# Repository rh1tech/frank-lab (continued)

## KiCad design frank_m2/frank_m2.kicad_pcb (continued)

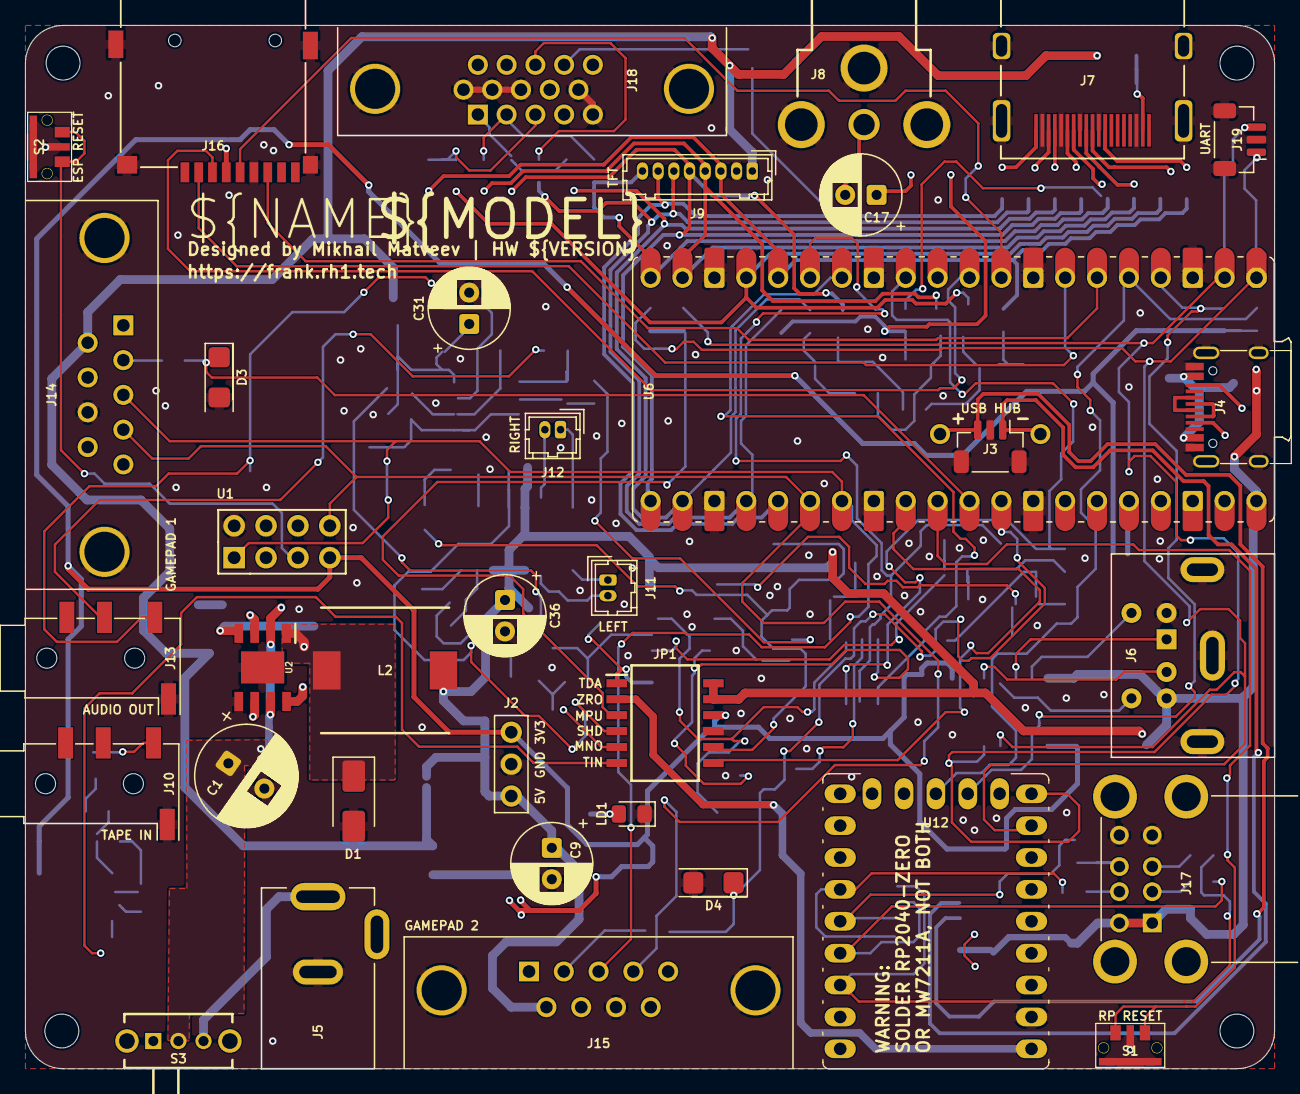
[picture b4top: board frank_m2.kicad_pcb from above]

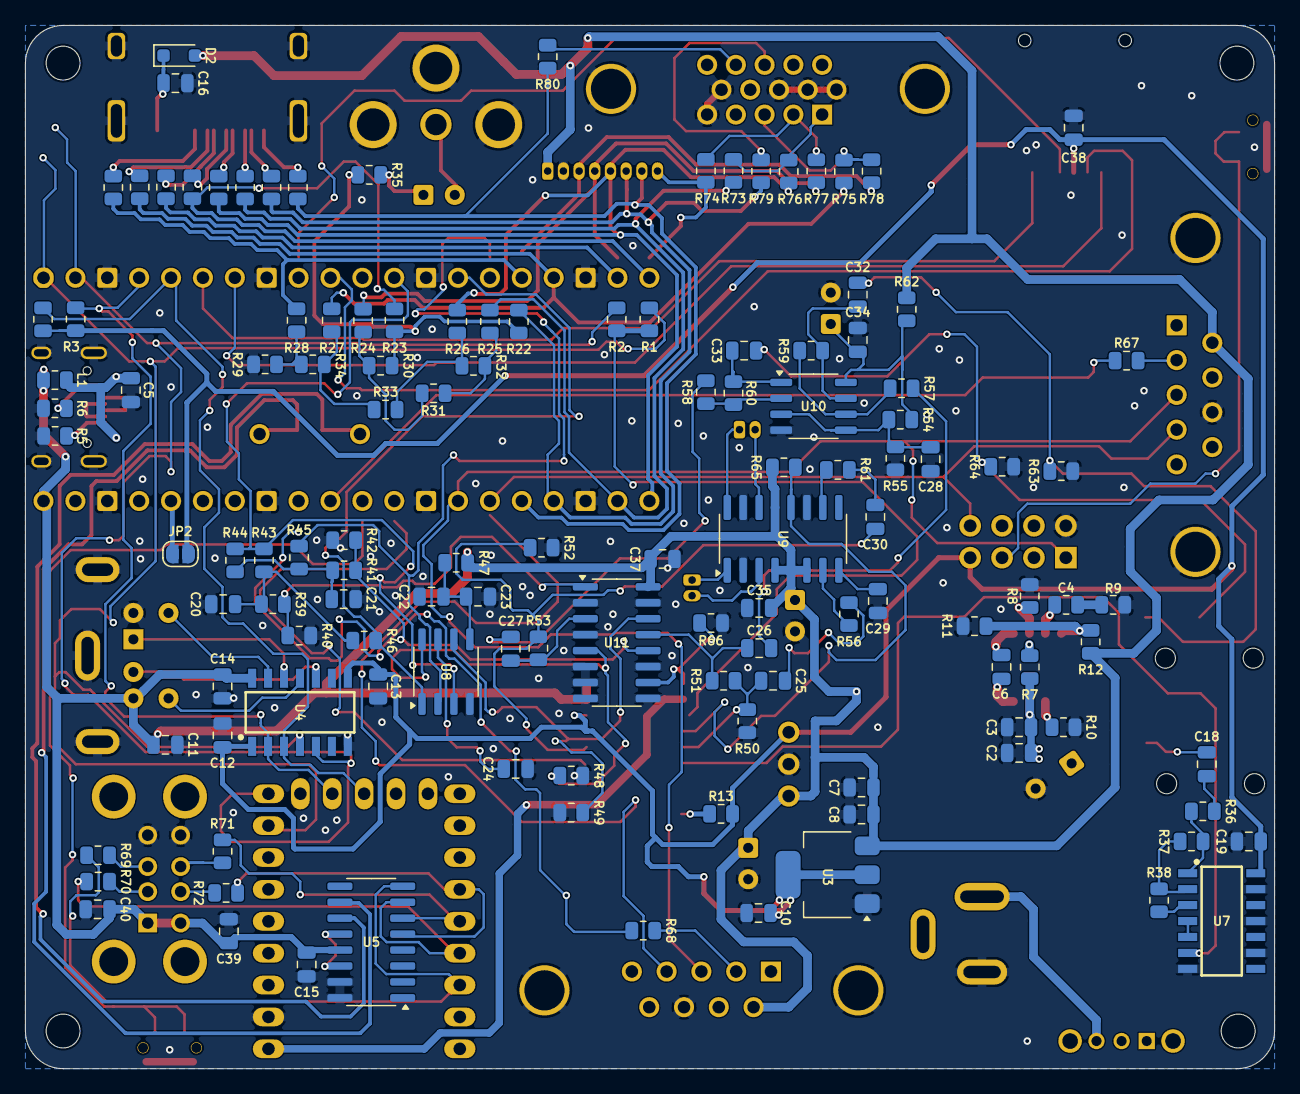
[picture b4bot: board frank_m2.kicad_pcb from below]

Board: 2 copper layers, 99.5 x 83.1 mm, 166 parts (126 on the bottom side), 126 nets.

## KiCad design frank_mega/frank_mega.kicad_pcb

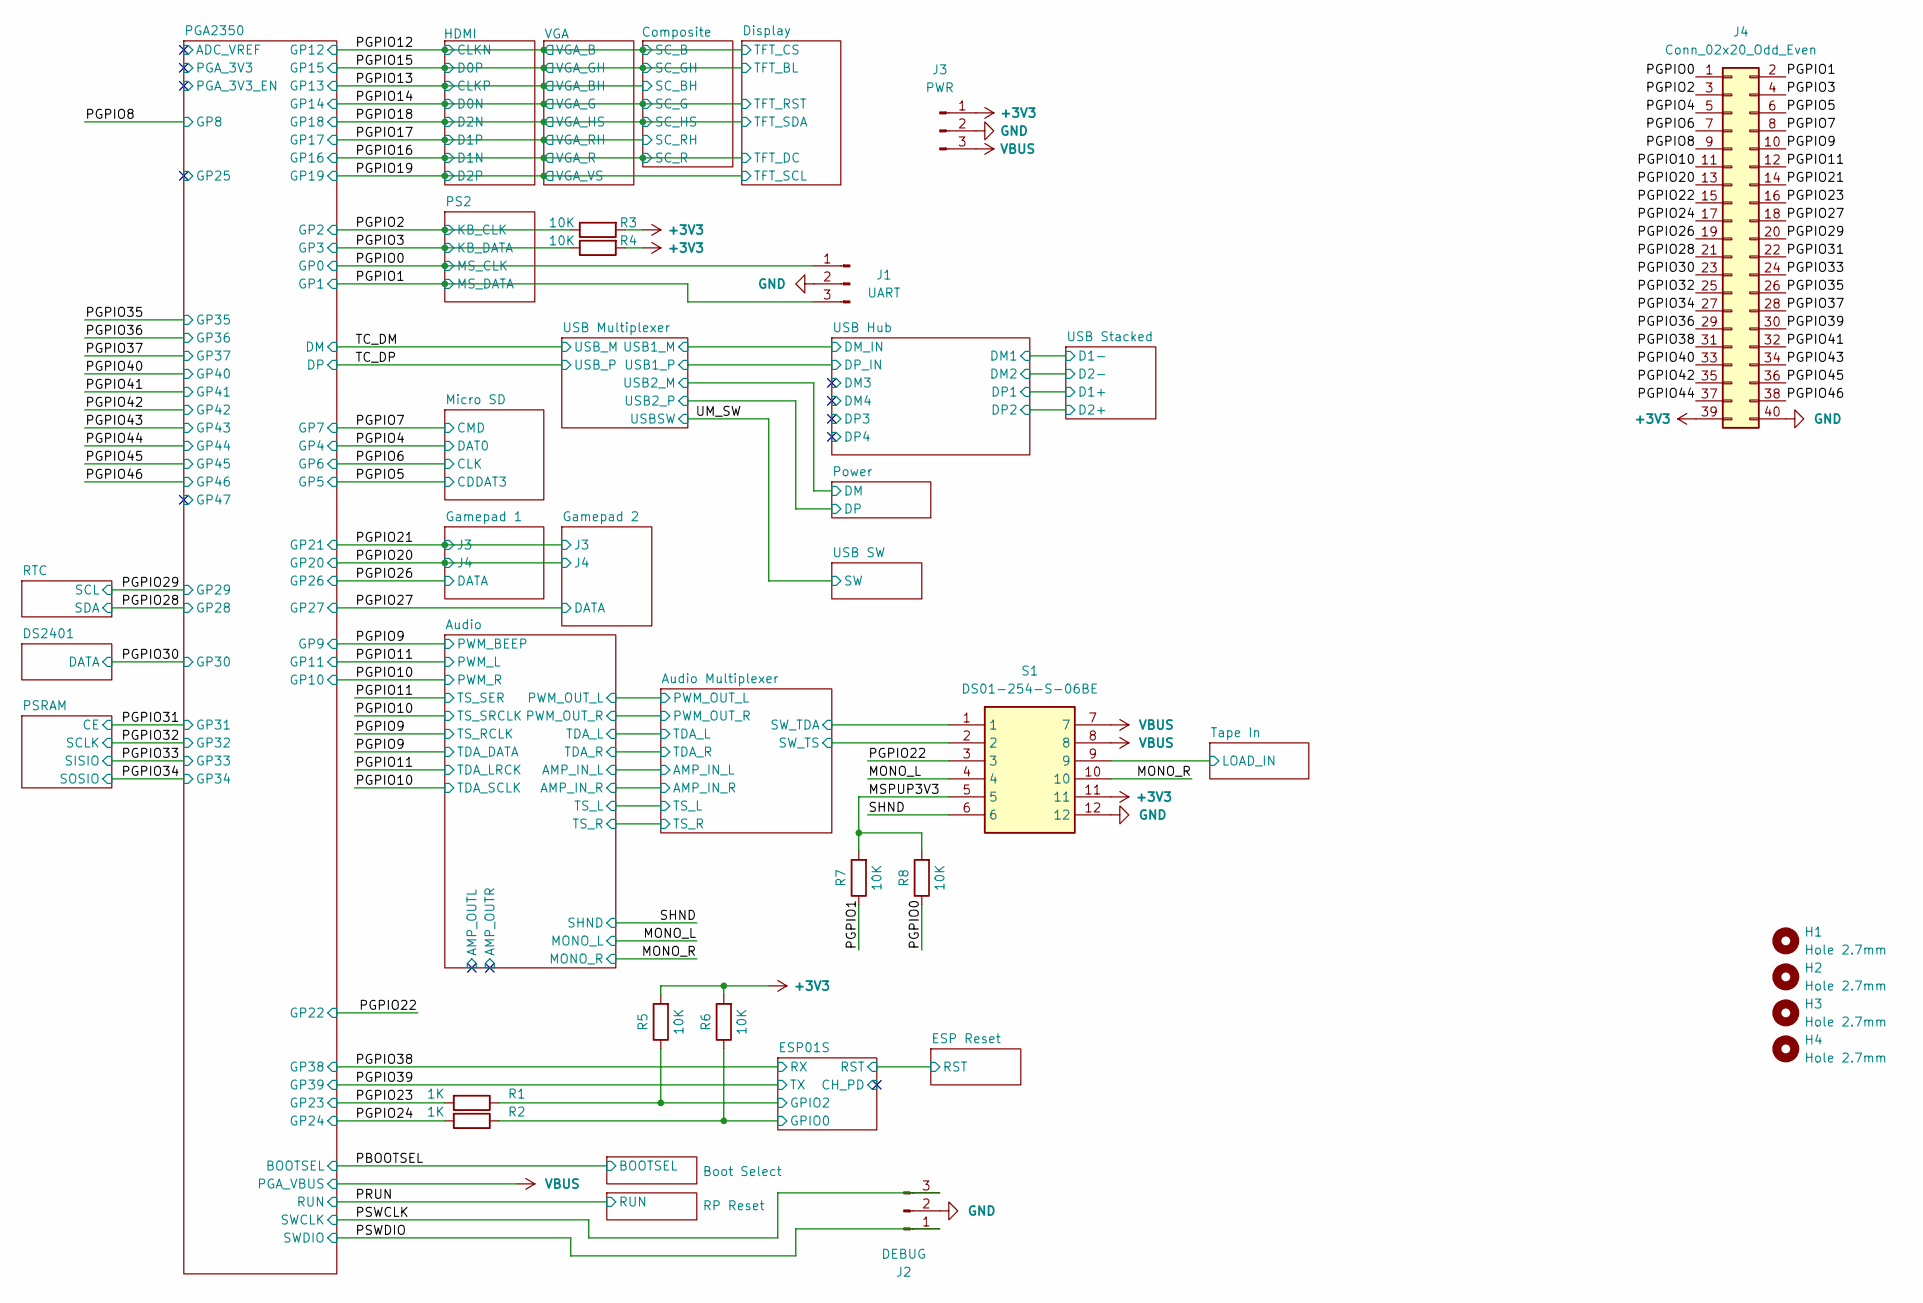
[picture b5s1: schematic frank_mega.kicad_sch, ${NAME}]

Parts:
H1, H2, H3, H4: Hole 2.7mm; MountingHole_2.7mm
J1: UART; JST_SH_1x03_P1.00mm_Vertical
J2: DEBUG; JST_SH_1x03_P1.00mm_Vertical
J3: PWR; PinHeader_1x03_P2.54mm
J4: Conn_02x20_Odd_Even; PinHeader_2x20_P2.54mm_Vertical
R1, R2: 1K; R_0805_2012Metric
R3, R4, R5, R6, R7, R8: 10K; R_0805_2012Metric
S1: DS01-254-S-06BE; Manufacturer_Part_Number DS01-254-S-06BE

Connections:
+3V3: J3.1, J4.39, R3.2, R4.2, R5.2, R6.2, S1.11; also elsewhere on the board
/Audio Multiplexer/SW_TDA: S1.1; also elsewhere on the board
/Audio Multiplexer/SW_TS: S1.2; also elsewhere on the board
/ESP01S/GPIO0: R2.1, R6.1; also elsewhere on the board
/ESP01S/GPIO2: R1.1, R5.1; also elsewhere on the board
/MONO_L: S1.4; also elsewhere on the board
/MONO_R: S1.10; also elsewhere on the board
/MSPUP3V3: R7.2, R8.2, S1.5
/PGPIO0: J1.1, J4.1, R8.1; also elsewhere on the board
/PGPIO1: J1.3, J4.2, R7.1; also elsewhere on the board
/PGPIO2: J4.3, R3.1; also elsewhere on the board
/PGPIO3: J4.4, R4.1; also elsewhere on the board
/PGPIO4: J4.5; also elsewhere on the board
/PGPIO5: J4.6; also elsewhere on the board
/PGPIO6: J4.7; also elsewhere on the board
/PGPIO7: J4.8; also elsewhere on the board
/PGPIO8: J4.9; also elsewhere on the board
/PGPIO9: J4.10; also elsewhere on the board
/PGPIO10: J4.11; also elsewhere on the board
/PGPIO11: J4.12; also elsewhere on the board
/PGPIO20: J4.13; also elsewhere on the board
/PGPIO21: J4.14; also elsewhere on the board
/PGPIO22: J4.15, S1.3; also elsewhere on the board
/PGPIO23: J4.16, R1.2; also elsewhere on the board
/PGPIO24: J4.17, R2.2; also elsewhere on the board
/PGPIO26: J4.19; also elsewhere on the board
/PGPIO27: J4.18; also elsewhere on the board
/PGPIO28: J4.21; also elsewhere on the board
/PGPIO29: J4.20; also elsewhere on the board
/PGPIO30: J4.23; also elsewhere on the board
/PGPIO31: J4.22; also elsewhere on the board
/PGPIO32: J4.25; also elsewhere on the board
/PGPIO33: J4.24; also elsewhere on the board
/PGPIO34: J4.27; also elsewhere on the board
/PGPIO35: J4.26; also elsewhere on the board
/PGPIO36: J4.29; also elsewhere on the board
/PGPIO37: J4.28; also elsewhere on the board
/PGPIO38: J4.31; also elsewhere on the board
/PGPIO39: J4.30; also elsewhere on the board
/PGPIO40: J4.33; also elsewhere on the board
/PGPIO41: J4.32; also elsewhere on the board
/PGPIO42: J4.35; also elsewhere on the board
/PGPIO43: J4.34; also elsewhere on the board
/PGPIO44: J4.37; also elsewhere on the board
/PGPIO45: J4.36; also elsewhere on the board
/PGPIO46: J4.38; also elsewhere on the board
/PSWCLK: J2.3; also elsewhere on the board
/PSWDIO: J2.1; also elsewhere on the board
/SHND: S1.6; also elsewhere on the board
/Tape In/LOAD_IN: S1.9; also elsewhere on the board
GND: J1.2, J2.2, J3.2, J4.40, S1.12; also elsewhere on the board
VBUS: J3.3, S1.7, S1.8; also elsewhere on the board

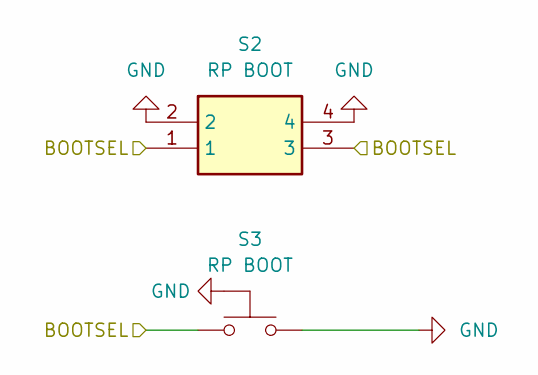
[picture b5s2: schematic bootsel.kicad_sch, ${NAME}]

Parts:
S2: RP BOOT; Button_SMD_3x4x2mm; Mouser Part Number 611-KMR221G-LFS
S3: RP BOOT; Button_SMD_TS1234VW

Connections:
/PBOOTSEL: S2.1, S2.3, S3.1; also elsewhere on the board
GND: S2.2, S2.4, S3.2, S3.3 (GND); also elsewhere on the board

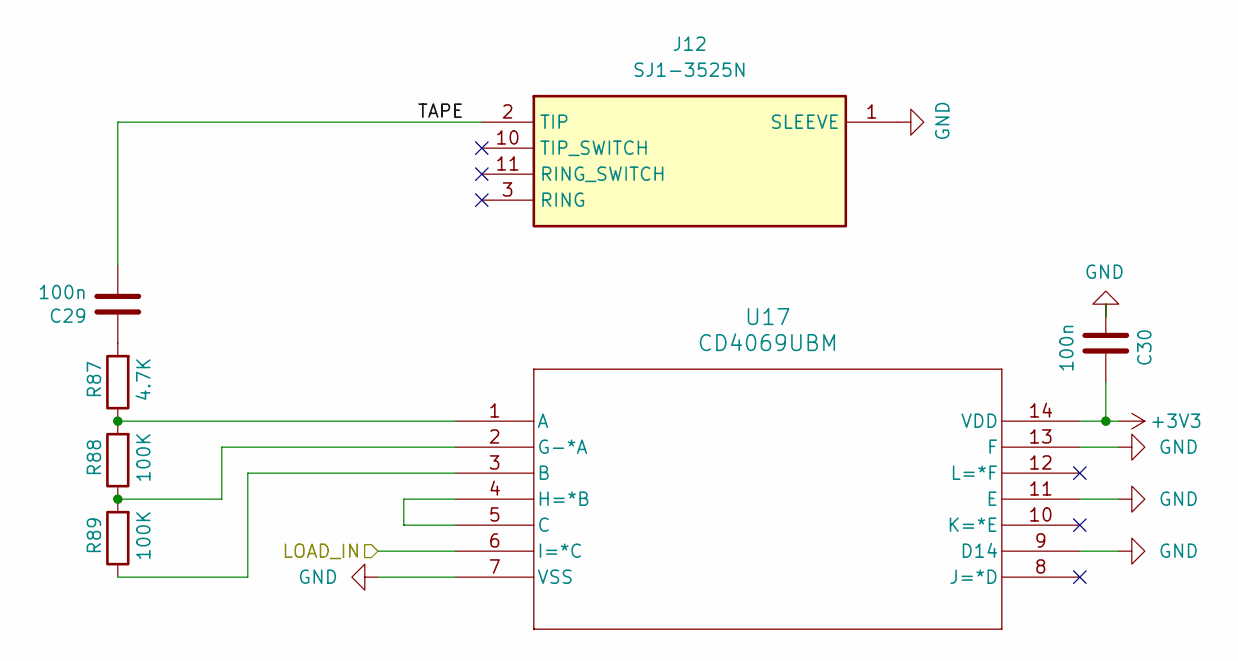
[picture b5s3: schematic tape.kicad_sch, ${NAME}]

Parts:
C29, C30: 100n; C_0805_2012Metric
J12: SJ1-3525N; AudioJack_3.5mm_SJ1-3525N; Mouser Part Number 490-SJ1-3525N
R87: 4.7K; R_0805_2012Metric
R88, R89: 100K; R_0805_2012Metric
U17: CD4069UBM; SOIC-14_P1.27mm

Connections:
+3V3: C30.1, U17.14 (VDD); also elsewhere on the board
/Tape In/LOAD_IN: U17.6 (I=*C); also elsewhere on the board
/Tape In/TAPE: C29.2, J12.2 (TIP)
GND: C30.2, J12.1 (SLEEVE), U17.7 (VSS), U17.9 (D14), U17.11 (E), U17.13 (F); also elsewhere on the board
unnamed: C29.1, R87.2
unnamed: R87.1, R88.2, U17.1 (A)
unnamed: R89.1, U17.3 (B)
unnamed: U17.4 (H=*B), U17.5 (C)
unnamed: R88.1, R89.2, U17.2 (G-*A)

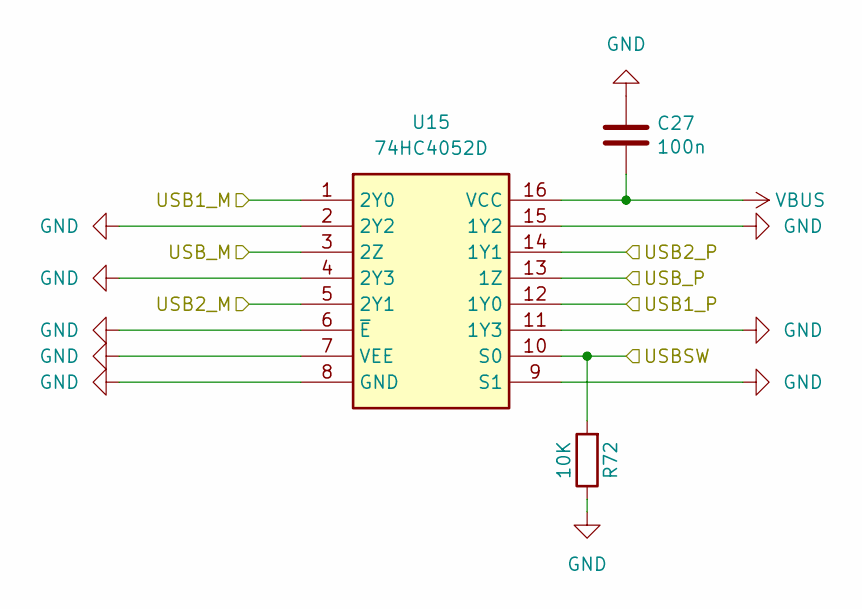
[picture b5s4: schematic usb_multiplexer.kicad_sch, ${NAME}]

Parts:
C27: 100n; C_0805_2012Metric
R72: 10K; R_0805_2012Metric
U15: 74HC4052D; SOP-16_P1.27mm; Mouser Part Number 771-74HC4052D-T

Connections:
/Power/DM: U15.5 (2Y1); also elsewhere on the board
/Power/DP: U15.14 (1Y1); also elsewhere on the board
/TC_DM: U15.3 (2Z); also elsewhere on the board
/TC_DP: U15.13 (1Z); also elsewhere on the board
/UM_SW: R72.2, U15.10 (S0); also elsewhere on the board
/USB Hub/DM_IN: U15.1 (2Y0); also elsewhere on the board
/USB Hub/DP_IN: U15.12 (1Y0); also elsewhere on the board
GND: C27.1, R72.1, U15.2 (2Y2), U15.4 (2Y3), U15.6 (~E), U15.7 (VEE), U15.8 (GND), U15.9 (S1), U15.11 (1Y3), U15.15 (1Y2); also elsewhere on the board
VBUS: C27.2, U15.16 (VCC); also elsewhere on the board

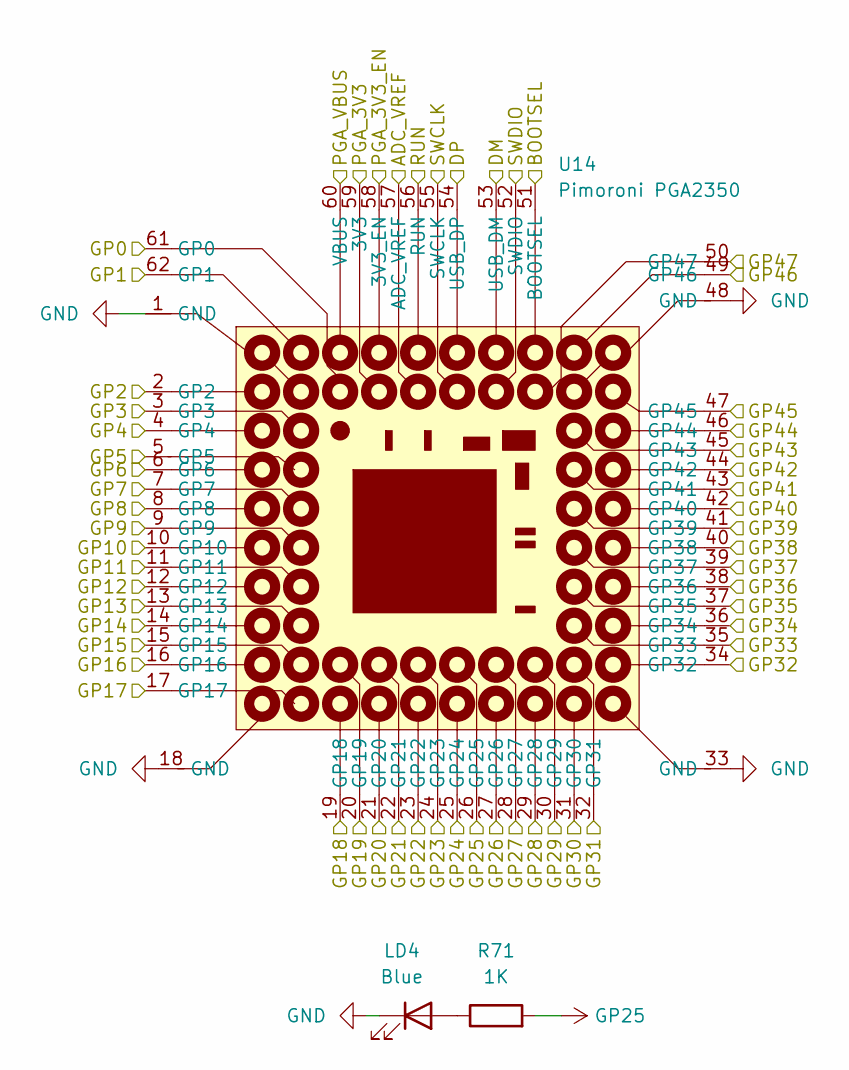
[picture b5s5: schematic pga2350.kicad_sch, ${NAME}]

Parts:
LD4: Blue; LED_0805
R71: 1K; R_0805_2012Metric
U14: Pimoroni PGA2350; PGA2350

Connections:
/PBOOTSEL: U14.51 (BOOTSEL); also elsewhere on the board
/PGA2350/ADC_VREF: U14.57 (ADC_VREF)
/PGA2350/GP47: U14.50 (GP47)
/PGA2350/PGA_3V3: U14.59 (3V3)
/PGA2350/PGA_3V3_EN: U14.58 (3V3_EN)
/PGPIO0: U14.61 (GP0); also elsewhere on the board
/PGPIO1: U14.62 (GP1); also elsewhere on the board
/PGPIO2: U14.2 (GP2); also elsewhere on the board
/PGPIO3: U14.3 (GP3); also elsewhere on the board
/PGPIO4: U14.4 (GP4); also elsewhere on the board
/PGPIO5: U14.5 (GP5); also elsewhere on the board
/PGPIO6: U14.6 (GP6); also elsewhere on the board
/PGPIO7: U14.7 (GP7); also elsewhere on the board
/PGPIO8: U14.8 (GP8); also elsewhere on the board
/PGPIO9: U14.9 (GP9); also elsewhere on the board
/PGPIO10: U14.10 (GP10); also elsewhere on the board
/PGPIO11: U14.11 (GP11); also elsewhere on the board
/PGPIO12: U14.12 (GP12); also elsewhere on the board
/PGPIO13: U14.13 (GP13); also elsewhere on the board
/PGPIO14: U14.14 (GP14); also elsewhere on the board
/PGPIO15: U14.15 (GP15); also elsewhere on the board
/PGPIO16: U14.16 (GP16); also elsewhere on the board
/PGPIO17: U14.17 (GP17); also elsewhere on the board
/PGPIO18: U14.19 (GP18); also elsewhere on the board
/PGPIO19: U14.20 (GP19); also elsewhere on the board
/PGPIO20: U14.21 (GP20); also elsewhere on the board
/PGPIO21: U14.22 (GP21); also elsewhere on the board
/PGPIO22: U14.23 (GP22); also elsewhere on the board
/PGPIO23: U14.24 (GP23); also elsewhere on the board
/PGPIO24: U14.25 (GP24); also elsewhere on the board
/PGPIO26: U14.27 (GP26); also elsewhere on the board
/PGPIO27: U14.28 (GP27); also elsewhere on the board
/PGPIO28: U14.29 (GP28); also elsewhere on the board
/PGPIO29: U14.30 (GP29); also elsewhere on the board
/PGPIO30: U14.31 (GP30); also elsewhere on the board
/PGPIO31: U14.32 (GP31); also elsewhere on the board
/PGPIO32: U14.34 (GP32); also elsewhere on the board
/PGPIO33: U14.35 (GP33); also elsewhere on the board
/PGPIO34: U14.36 (GP34); also elsewhere on the board
/PGPIO35: U14.37 (GP35); also elsewhere on the board
/PGPIO36: U14.38 (GP36); also elsewhere on the board
/PGPIO37: U14.39 (GP37); also elsewhere on the board
/PGPIO38: U14.40 (GP38); also elsewhere on the board
/PGPIO39: U14.41 (GP39); also elsewhere on the board
/PGPIO40: U14.42 (GP40); also elsewhere on the board
/PGPIO41: U14.43 (GP41); also elsewhere on the board
/PGPIO42: U14.44 (GP42); also elsewhere on the board
/PGPIO43: U14.45 (GP43); also elsewhere on the board
/PGPIO44: U14.46 (GP44); also elsewhere on the board
/PGPIO45: U14.47 (GP45); also elsewhere on the board
/PGPIO46: U14.49 (GP46); also elsewhere on the board
/PRUN: U14.56 (RUN); also elsewhere on the board
/PSWCLK: U14.55 (SWCLK); also elsewhere on the board
/PSWDIO: U14.52 (SWDIO); also elsewhere on the board
/TC_DM: U14.53 (USB_DM); also elsewhere on the board
/TC_DP: U14.54 (USB_DP); also elsewhere on the board
GND: LD4.1 (K), U14.1 (GND), U14.18 (GND), U14.33 (GND), U14.48 (GND); also elsewhere on the board
GP25: R71.2, U14.26 (GP25)
unnamed: LD4.2 (A), R71.1
VBUS: U14.60 (VBUS); also elsewhere on the board

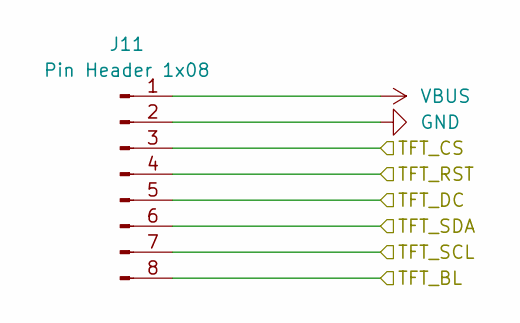
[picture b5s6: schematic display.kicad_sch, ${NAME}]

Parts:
J11: Pin Header 1x08; JST_GH_1x08_P1.25mm

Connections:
/PGPIO12: J11.3; also elsewhere on the board
/PGPIO14: J11.4; also elsewhere on the board
/PGPIO15: J11.8; also elsewhere on the board
/PGPIO16: J11.5; also elsewhere on the board
/PGPIO18: J11.6; also elsewhere on the board
/PGPIO19: J11.7; also elsewhere on the board
GND: J11.2; also elsewhere on the board
VBUS: J11.1; also elsewhere on the board

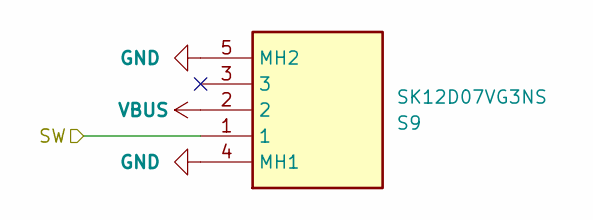
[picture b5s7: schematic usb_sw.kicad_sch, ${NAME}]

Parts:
S9: SK12D07VG3NS; Switch_Slide_SK12D07VG3NS; Mouser Part Number 611-SK12D07VG3NS

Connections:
/UM_SW: S9.1; also elsewhere on the board
GND: S9.4 (MH1), S9.5 (MH2); also elsewhere on the board
VBUS: S9.2; also elsewhere on the board

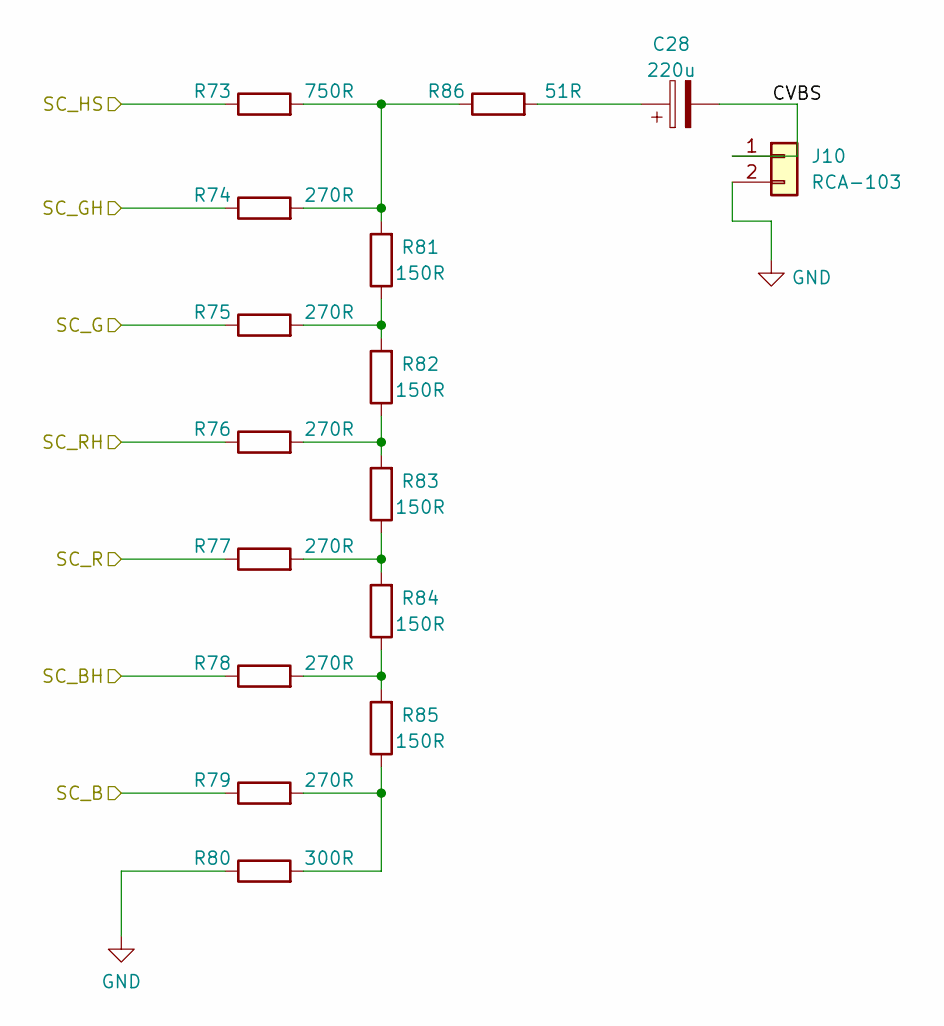
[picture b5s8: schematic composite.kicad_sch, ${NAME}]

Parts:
C28: 220u; C_Radial_D6.3mm_P2.50mm
J10: RCA-103; BarrelJack_RCJ-012
R73: 750R; R_0805_2012Metric
R74, R75, R76, R77, R78, R79: 270R; R_0805_2012Metric
R80: 300R; R_0805_2012Metric
R81, R82, R83, R84, R85: 150R; R_0805_2012Metric
R86: 51R; R_0805_2012Metric

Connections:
/Composite/CVBS: C28.2, J10.1
/PGPIO12: R79.1; also elsewhere on the board
/PGPIO13: R78.1; also elsewhere on the board
/PGPIO14: R75.1; also elsewhere on the board
/PGPIO15: R74.1; also elsewhere on the board
/PGPIO16: R77.1; also elsewhere on the board
/PGPIO17: R76.1; also elsewhere on the board
/PGPIO18: R73.1; also elsewhere on the board
GND: J10.2, R80.1; also elsewhere on the board
unnamed: C28.1, R86.2
unnamed: R73.2, R74.2, R81.2, R86.1
unnamed: R75.2, R81.1, R82.2
unnamed: R76.2, R82.1, R83.2
unnamed: R77.2, R83.1, R84.2
unnamed: R78.2, R84.1, R85.2
unnamed: R79.2, R80.2, R85.1

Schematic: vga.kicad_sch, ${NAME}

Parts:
J20: VGA; DSUB-15_Female
R125, R126, R127: 330R; R_0805_2012Metric
R128, R129, R130: 1K; R_0805_2012Metric
R131, R132: 100R; R_0805_2012Metric

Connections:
/PGPIO12: R130.1; also elsewhere on the board
/PGPIO13: R127.1; also elsewhere on the board
/PGPIO14: R129.1; also elsewhere on the board
/PGPIO15: R126.1; also elsewhere on the board
/PGPIO16: R128.1; also elsewhere on the board
/PGPIO17: R125.1; also elsewhere on the board
/PGPIO18: R131.2; also elsewhere on the board
/PGPIO19: R132.2; also elsewhere on the board
GND: J20.0, J20.5, J20.6, J20.7, J20.8, J20.10; also elsewhere on the board
unnamed: J20.1, R125.2, R128.2
unnamed: J20.2, R126.2, R129.2
unnamed: J20.3, R127.2, R130.2
unnamed: J20.13, R131.1
unnamed: J20.14, R132.1

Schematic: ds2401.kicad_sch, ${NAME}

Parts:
R62: 4.7K; R_0805_2012Metric
U11: DS2401P+; TSOC-6; Mouser Part Number 700-DS2401P

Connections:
+3V3: R62.1; also elsewhere on the board
/PGPIO30: R62.2, U11.2 (DATA); also elsewhere on the board
GND: U11.1 (GND); also elsewhere on the board

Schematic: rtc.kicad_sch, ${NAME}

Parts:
C23: 100n; C_0805_2012Metric
H5: Battery_CR1220; Manufacturer_Part_Number 1174
J8: BAT 3V; PinHeader_1x02_P2.54mm_Vertical
R60, R61: 4.7K; R_0805_2012Metric
U10: DS3231MZ; SOIC-8_3.9x4.9mm_P1.27mm

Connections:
+3V3: C23.1, R60.2, R61.2, U10.2 (VCC); also elsewhere on the board
/PGPIO28: R61.1, U10.7 (SDA); also elsewhere on the board
/PGPIO29: R60.1, U10.8 (SCL); also elsewhere on the board
GND: C23.2, H5.2 (-), J8.2, U10.5 (GND); also elsewhere on the board
unnamed: H5.1 (+), J8.1, U10.6 (VBAT)

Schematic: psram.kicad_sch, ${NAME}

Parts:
C25: 100n; C_0805_2012Metric
S10: PSRAM On; SolderJumper-2_P1.3mm_Open_RoundedPad1.0x1.5mm
U12: ESP-PSRAM64; SO-8

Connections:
+3V3: C25.1, U12.8 (VCC); also elsewhere on the board
/PGPIO31: U12.1 (~CE); also elsewhere on the board
/PGPIO32: U12.6 (SCLK); also elsewhere on the board
/PGPIO33: U12.5 (SI/SIO); also elsewhere on the board
/PGPIO34: S10.2 (B); also elsewhere on the board
GND: C25.2, U12.4 (VSS); also elsewhere on the board
unnamed: S10.1 (A), U12.2 (SO/SIO)

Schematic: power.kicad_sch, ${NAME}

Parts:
C1: 680u; C_Radial_D8.0mm_P3.50mm
C2, C7, C10: 10u; C_0805_2012Metric
C3, C5, C6, C9: 100n; C_0805_2012Metric
C4: 150pF; R_0805_2012Metric
C8: 220u; C_Radial_D6.3mm_P2.50mm
D1: 1N5822; D_SMA
J5: DC-005-5A-2.0; BarrelJack_DC-005; PARTREV A0
J6: USB4215-03-A; USB_C_Receptacle
L1: 22uH; Inductor_CDRH104RNP
L2: 330R; C_0805_2012Metric
LD1: Green; LED_0805
R9, R11, R12: 100K; R_0805_2012Metric
R10: 24K; R_0805_2012Metric
R13, R14: 5.1K; R_0805_2012Metric
R15: 8.2K; R_0805_2012Metric
R16: 1M; R_0805_2012Metric
R17: 43K; R_0805_2012Metric
R18, R19: 22R; R_0805_2012Metric
R20: 1K; R_0805_2012Metric
S4: SK12D07VG3NS; Switch_Slide_SK12D07VG3NS; Mouser Part Number 611-SK12D07VG3NS
U1: MP1584EN-LF-Z; SOIC-9_P1.27mm; Mouser Part Number 946-MP1584ENLFZ
U2: USBLC6-2SC6; SOT-23-6
U3: AMS1117 3.3; SOT-223-3_TabPin2

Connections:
+3V3: C10.1, R20.2, U3.2 (VO); also elsewhere on the board
/Power/D+: J6.6 (DP1), J6.8 (DP2), R19.2
/Power/D-: J6.5 (DN2), J6.7 (DN1), R18.2
/Power/DM: U2.6 (I/O1); also elsewhere on the board
/Power/DP: U2.4 (I/O2); also elsewhere on the board
/Power/VBUS_IN: C1.1, C2.1, C3.1, R9.2, S4.2, U1.7 (VIN)
GND: C1.2, C2.2, C3.2, C6.1, C7.2, C8.2, C9.2, C10.2, D1.2 (A), J5.2, J6.1 (GND), J6.12 (GND), LD1.1 (K), R10.2, R11.2, R12.2, R13.1, R14.1, R15.1, R16.1, U1.5 (GND), U1.9 (EP), U2.2 (GND), U3.1 (GND); also elsewhere on the board
unnamed: C4.2, R11.1
unnamed: C9.1, J6.2 (VBUS), J6.11 (VBUS), L2.2
unnamed: C5.2, D1.1 (K), L1.1, U1.1 (SW)
unnamed: J5.1, S4.3
unnamed: J6.4 (CC1), R13.2
unnamed: J6.10 (CC2), R14.2
unnamed: J6.13 (SHIELD), R16.2
unnamed: LD1.2 (A), R20.1
unnamed: R18.1, U2.1 (I/O1)
unnamed: R19.1, U2.3 (I/O2)
unnamed: C5.1, U1.8 (BST)
unnamed: C4.1, U1.3 (COMP)
unnamed: R9.1, R10.1, U1.2 (EN)
unnamed: R15.2, R17.2, U1.4 (FB)
unnamed: R12.1, U1.6 (FREQ)
VBUS: C6.2, C7.1, C8.1, L1.2, L2.1, R17.1, U2.5 (VBUS), U3.3 (VI); also elsewhere on the board

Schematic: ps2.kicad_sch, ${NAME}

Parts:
C11, C12, C13, C14: 100n; C_0805_2012Metric
J7: MDC-036; MiniDIN_6pin_Female
U4: TXS0104EDR; SOIC-14_P1.27mm; Mouser Part Number 595-TXS0104EDR

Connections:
+3V3: C12.1, C13.1, U4.1 (VCCA), U4.8 (OE); also elsewhere on the board
/PGPIO0: U4.4 (A3); also elsewhere on the board
/PGPIO1: U4.5 (A4); also elsewhere on the board
/PGPIO2: U4.2 (A1); also elsewhere on the board
/PGPIO3: U4.3 (A2); also elsewhere on the board
/PS2/KB_CLK_5V: J7.5, U4.13 (B1)
/PS2/KB_DATA_5V: J7.1, U4.12 (B2)
/PS2/MS_CLK_5V: J7.6, U4.11 (B3)
/PS2/MS_DATA_5V: J7.2, U4.10 (B4)
GND: C11.2, C12.2, C13.2, C14.2, J7.3, U4.7 (GND); also elsewhere on the board
VBUS: C11.1, C14.1, J7.4, U4.14 (VCCB); also elsewhere on the board

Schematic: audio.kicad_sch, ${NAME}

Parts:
J13: PAM L; JST_GH_1x02_P1.25mm
J14: PAM R; JST_GH_1x02_P1.25mm
J15: SJ1-3525N; AudioJack_3.5mm_SJ1-3525N; Mouser Part Number 490-SJ1-3525N

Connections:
/Audio/AMP_OUTL: J15.2 (TIP); also elsewhere on the board
/Audio/AMP_OUTR: J15.3 (RING); also elsewhere on the board
/Audio/AMP_PAM_OUTL_M: J13.2; also elsewhere on the board
/Audio/AMP_PAM_OUTL_P: J13.1; also elsewhere on the board
/Audio/AMP_PAM_OUTR_M: J14.2; also elsewhere on the board
/Audio/AMP_PAM_OUTR_P: J14.1; also elsewhere on the board
GND: J15.1 (SLEEVE); also elsewhere on the board

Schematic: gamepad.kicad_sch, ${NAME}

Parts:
D5: 3V3; D_MiniMELF
J16: GP2; DSUB-9_Male_TopMount
R119: 1K; R_0805_2012Metric

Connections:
/PGPIO20: J16.4; also elsewhere on the board
/PGPIO21: J16.3; also elsewhere on the board
/PGPIO26: D5.1 (K), R119.1; also elsewhere on the board
GND: D5.2 (A), J16.8; also elsewhere on the board
unnamed: J16.2, R119.2
VBUS: J16.6; also elsewhere on the board

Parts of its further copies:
D6: 3V3; D_MiniMELF
J17: GP2; DSUB-9_Male_TopMount
R120: 1K; R_0805_2012Metric

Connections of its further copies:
/PGPIO20: J17.4; also elsewhere on the board
/PGPIO21: J17.3; also elsewhere on the board
/PGPIO27: D6.1 (K), R120.1; also elsewhere on the board
GND: D6.2 (A), J17.8; also elsewhere on the board
unnamed: J17.2, R120.2
VBUS: J17.6; also elsewhere on the board

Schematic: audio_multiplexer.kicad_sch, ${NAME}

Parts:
C48: 100n; C_0805_2012Metric
R117, R118: 10K; R_0805_2012Metric
U21: 74HC4052D; SOP-16_P1.27mm; Mouser Part Number 771-74HC4052D-T

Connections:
/Audio Multiplexer/AMP_IN_L: U21.13 (1Z); also elsewhere on the board
/Audio Multiplexer/AMP_IN_R: U21.3 (2Z); also elsewhere on the board
/Audio Multiplexer/PWM_OUT_L: U21.12 (1Y0); also elsewhere on the board
/Audio Multiplexer/PWM_OUT_R: U21.1 (2Y0); also elsewhere on the board
/Audio Multiplexer/SW_TDA: R117.2, U21.10 (S0); also elsewhere on the board
/Audio Multiplexer/SW_TS: R118.2, U21.9 (S1); also elsewhere on the board
/Audio Multiplexer/TDA_L: U21.14 (1Y1); also elsewhere on the board
/Audio Multiplexer/TDA_R: U21.5 (2Y1); also elsewhere on the board
/Audio/TS/L_IN: U21.15 (1Y2); also elsewhere on the board
/Audio/TS/R_IN: U21.2 (2Y2); also elsewhere on the board
GND: C48.1, R117.1, R118.1, U21.4 (2Y3), U21.6 (~E), U21.7 (VEE), U21.8 (GND), U21.11 (1Y3); also elsewhere on the board
VBUS: C48.2, U21.16 (VCC); also elsewhere on the board

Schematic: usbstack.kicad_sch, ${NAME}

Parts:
C50, C51: 10u; C_0805_2012Metric
J19: SS-52100-004; USB_A_Stacked
R121, R122, R123, R124: 22R; R_0805_2012Metric

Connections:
/USB Hub/DM1: R122.1; also elsewhere on the board
/USB Hub/DM2: R124.1; also elsewhere on the board
/USB Hub/DP1: R121.1; also elsewhere on the board
/USB Hub/DP2: R123.1; also elsewhere on the board
GND: C50.2, C51.2, J19.4 (GND1), J19.8 (GND2), J19.SH (Shield); also elsewhere on the board
unnamed: J19.3 (D1+), R121.2
unnamed: J19.2 (D1-), R122.2
unnamed: J19.7 (D2+), R123.2
unnamed: J19.6 (D2-), R124.2
VBUS: C50.1, C51.1, J19.1 (VBUS1), J19.5 (VBUS2); also elsewhere on the board

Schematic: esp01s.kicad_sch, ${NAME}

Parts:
U16: ESP-01v090; ESP-01S

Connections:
+3V3: U16.7 (VCC); also elsewhere on the board
/ESP01S/CH_PD: U16.3 (CH_PD)
/ESP01S/GPIO0: U16.6 (GPIO0); also elsewhere on the board
/ESP01S/GPIO2: U16.4 (GPIO2); also elsewhere on the board
/ESP Reset/RST: U16.5 (RST); also elsewhere on the board
/PGPIO38: U16.8 (URXD); also elsewhere on the board
/PGPIO39: U16.1 (UTXD); also elsewhere on the board
GND: U16.2 (GND); also elsewhere on the board

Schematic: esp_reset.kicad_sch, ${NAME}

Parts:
S6: ESP Reset; Button_SMD_TS1234VW

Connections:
/PRUN: S6.1; also elsewhere on the board
GND: S6.2, S6.3 (GND); also elsewhere on the board

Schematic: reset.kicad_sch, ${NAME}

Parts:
S5: RP Reset; Button_SMD_3x4x2mm; Mouser Part Number 611-KMR221G-LFS
S6: RP Reset; Button_SMD_TS1234VW

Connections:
/PRUN: S5.1, S5.3, S6.1; also elsewhere on the board
GND: S5.2, S5.4, S6.2, S6.3 (GND); also elsewhere on the board

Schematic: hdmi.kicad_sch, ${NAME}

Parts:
C24: 100n; C_0805_2012Metric
D4: 1N5819WS; D_SOD-323
J9: DC3RX19JA2; HDMI_Female
R63, R64, R65, R66, R67, R68, R69, R70: 270R; R_0805_2012Metric

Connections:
/PGPIO12: R65.2; also elsewhere on the board
/PGPIO13: R69.2; also elsewhere on the board
/PGPIO14: R63.2; also elsewhere on the board
/PGPIO15: R66.2; also elsewhere on the board
/PGPIO16: R67.2; also elsewhere on the board
/PGPIO17: R70.2; also elsewhere on the board
/PGPIO18: R64.2; also elsewhere on the board
/PGPIO19: R68.2; also elsewhere on the board
GND: C24.2, J9.2 (G_D2), J9.5 (G_D1), J9.8 (G_D0), J9.11 (G_CLK), J9.17 (G_DDC/CEC), J9.20 (SHIELD1), J9.21 (SHIELD2), J9.22 (SHIELD3), J9.23 (SHIELD4); also elsewhere on the board
unnamed: C24.1, D4.1 (K), J9.18 (+5V)
unnamed: J9.12 (CLKN), R65.1
unnamed: J9.10 (CLKP), R69.1
unnamed: J9.9 (D0N), R63.1
unnamed: J9.7 (D0P), R66.1
unnamed: J9.6 (D1N), R67.1
unnamed: J9.4 (D1P), R70.1
unnamed: J9.3 (D2N), R64.1
unnamed: J9.1 (D2P), R68.1
VBUS: D4.2 (A); also elsewhere on the board

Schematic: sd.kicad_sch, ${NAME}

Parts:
C49: 100n; C_0805_2012Metric
J18: 104031-0811; MicroSD_SMD_Long

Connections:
+3V3: C49.2, J18.4 (VDD); also elsewhere on the board
/PGPIO4: J18.7 (DAT0); also elsewhere on the board
/PGPIO5: J18.2 (DAT3/CD); also elsewhere on the board
/PGPIO6: J18.5 (CLK); also elsewhere on the board
/PGPIO7: J18.3 (CMD); also elsewhere on the board
GND: C49.1, J18.6 (VSS), J18.SH (SHIELD); also elsewhere on the board

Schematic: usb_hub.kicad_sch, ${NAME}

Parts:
C26: 4.7u; C_0805_2012Metric; LCSC C1746
U13: MW7211A; SOP-16_P1.27mm

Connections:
/USB Hub/DM1: U13.7 (DM3); also elsewhere on the board
/USB Hub/DM2: U13.5 (DM2); also elsewhere on the board
/USB Hub/DM3: U13.3 (DM1)
/USB Hub/DM4: U13.1 (DM0)
/USB Hub/DM_IN: U13.10 (DMU); also elsewhere on the board
/USB Hub/DP1: U13.8 (DP3); also elsewhere on the board
/USB Hub/DP2: U13.6 (DP2); also elsewhere on the board
/USB Hub/DP3: U13.4 (DP1)
/USB Hub/DP4: U13.2 (DP0)
/USB Hub/DP_IN: U13.11 (DPU); also elsewhere on the board
GND: C26.2, U13.15 (GND), U13.16 (GND); also elsewhere on the board
unnamed: U13.12 (VD33), U13.14 (VD3)
VBUS: C26.1, U13.13 (VDD5); also elsewhere on the board

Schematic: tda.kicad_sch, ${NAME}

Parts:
C33, C35: 10u; C_0805_2012Metric
C34: 100n; C_0805_2012Metric
R98: 100R; R_0805_2012Metric
R99, R100: 470R; R_0805_2012Metric
U18: TDA1387T; SO-8

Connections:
/Audio Multiplexer/TDA_L: R100.2, U18.6 (A_LEFT); also elsewhere on the board
/Audio Multiplexer/TDA_R: R99.1, U18.8 (A_RIGHT); also elsewhere on the board
/PGPIO9: U18.3 (DATA); also elsewhere on the board
/PGPIO10: U18.1 (SCLK); also elsewhere on the board
/PGPIO11: U18.2 (LRCK); also elsewhere on the board
GND: C33.2, C34.2, C35.2, R99.2, R100.1, U18.4 (AGND); also elsewhere on the board
unnamed: C35.1, U18.7 (FLT)
unnamed: C33.1, C34.1, R98.1, U18.5 (VA)
VBUS: R98.2; also elsewhere on the board
